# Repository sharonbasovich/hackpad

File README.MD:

# Sharon's Hackpad
This is a macropad that I made for HackClub's Highway program.

## Features
- 16 Switches (4x4 Matrix)
- 16 Neopixels
- An OLED Screen

## Hackpad

## Schematic

## PCB

## Case

## BOM
- 16x Cherry MX Switches
- 16x DSA Keycaps
- 16x 1N4148 Diodes
- 1x 0.91" 128x32 OLED Display
- 1x XIAO RP2040
- 1x Case Bottom Piece
- 1x Case Top Piece
- 4x M3x16mm Screws
- 4x M3x5mx4mm Heatset Inserts

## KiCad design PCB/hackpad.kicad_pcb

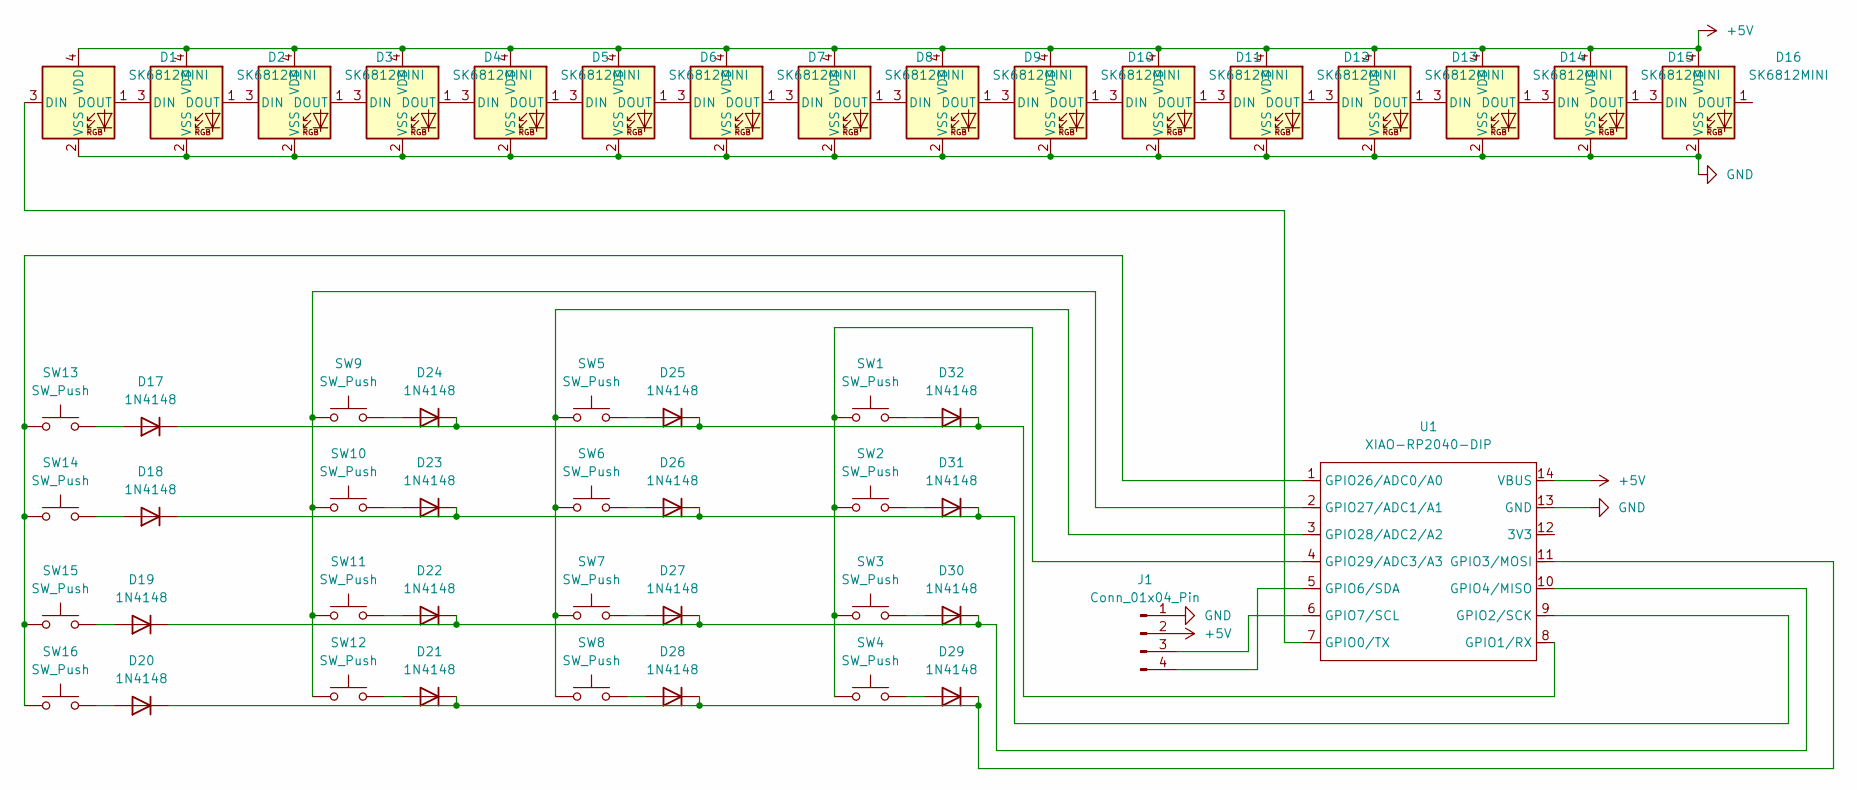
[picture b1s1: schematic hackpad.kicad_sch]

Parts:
D1, D2, D3, D4, D5, D6, D7, D8, D9, D10, D11, D12, D13, D14, D15, D16: SK6812MINI; LED_SK6812MINI_PLCC4_3.5x3.5mm_P1.75mm
D17, D18, D19, D20, D21, D22, D23, D24, D25, D26, D27, D28, D29, D30, D31, D32: 1N4148; D_DO-35_SOD27_P7.62mm_Horizontal
J1: Conn_01x04_Pin; SSD1306-0.91-OLED-4pin-128x32
SW1, SW2, SW3, SW4, SW5, SW6, SW7, SW8, SW9, SW10, SW11, SW12, SW13, SW14, SW15, SW16: SW_Push; SW_Cherry_MX_1.00u_PCB
U1: XIAO-RP2040-DIP

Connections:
+5V: D1.4 (VDD), D2.4 (VDD), D3.4 (VDD), D4.4 (VDD), D5.4 (VDD), D6.4 (VDD), D7.4 (VDD), D8.4 (VDD), D9.4 (VDD), D10.4 (VDD), D11.4 (VDD), D12.4 (VDD), D13.4 (VDD), D14.4 (VDD), D15.4 (VDD), D16.4 (VDD), J1.2, U1.14 (VBUS)
GND: D1.2 (VSS), D2.2 (VSS), D3.2 (VSS), D4.2 (VSS), D5.2 (VSS), D6.2 (VSS), D7.2 (VSS), D8.2 (VSS), D9.2 (VSS), D10.2 (VSS), D11.2 (VSS), D12.2 (VSS), D13.2 (VSS), D14.2 (VSS), D15.2 (VSS), D16.2 (VSS), J1.1, U1.13 (GND)
unnamed: D1.3 (DIN), U1.7 (GPIO0/TX)
unnamed: D1.1 (DOUT), D2.3 (DIN)
unnamed: D2.1 (DOUT), D3.3 (DIN)
unnamed: D3.1 (DOUT), D4.3 (DIN)
unnamed: D4.1 (DOUT), D5.3 (DIN)
unnamed: D5.1 (DOUT), D6.3 (DIN)
unnamed: D6.1 (DOUT), D7.3 (DIN)
unnamed: D7.1 (DOUT), D8.3 (DIN)
unnamed: D8.1 (DOUT), D9.3 (DIN)
unnamed: D9.1 (DOUT), D10.3 (DIN)
unnamed: D10.1 (DOUT), D11.3 (DIN)
unnamed: D11.1 (DOUT), D12.3 (DIN)
unnamed: D12.1 (DOUT), D13.3 (DIN)
unnamed: D13.1 (DOUT), D14.3 (DIN)
unnamed: D14.1 (DOUT), D15.3 (DIN)
unnamed: D15.1 (DOUT), D16.3 (DIN)
unnamed: D17.2 (A), SW13.2
unnamed: D17.1 (K), D24.1 (K), D25.1 (K), D32.1 (K), U1.8 (GPIO1/RX)
unnamed: D18.2 (A), SW14.2
unnamed: D18.1 (K), D23.1 (K), D26.1 (K), D31.1 (K), U1.9 (GPIO2/SCK)
unnamed: D19.2 (A), SW15.2
unnamed: D19.1 (K), D22.1 (K), D27.1 (K), D30.1 (K), U1.10 (GPIO4/MISO)
unnamed: D20.2 (A), SW16.2
unnamed: D20.1 (K), D21.1 (K), D28.1 (K), D29.1 (K), U1.11 (GPIO3/MOSI)
unnamed: D21.2 (A), SW12.2
unnamed: D22.2 (A), SW11.2
unnamed: D23.2 (A), SW10.2
unnamed: D24.2 (A), SW9.2
unnamed: D25.2 (A), SW5.2
unnamed: D26.2 (A), SW6.2
unnamed: D27.2 (A), SW7.2
unnamed: D28.2 (A), SW8.2
unnamed: D29.2 (A), SW4.2
unnamed: D30.2 (A), SW3.2
unnamed: D31.2 (A), SW2.2
unnamed: D32.2 (A), SW1.2
unnamed: J1.3, U1.6 (GPIO7/SCL)
unnamed: J1.4, U1.5 (GPIO6/SDA)
unnamed: SW13.1, SW14.1, SW15.1, SW16.1, U1.1 (GPIO26/ADC0/A0)
unnamed: SW9.1, SW10.1, SW11.1, SW12.1, U1.2 (GPIO27/ADC1/A1)
unnamed: SW5.1, SW6.1, SW7.1, SW8.1, U1.3 (GPIO28/ADC2/A2)
unnamed: SW1.1, SW2.1, SW3.1, SW4.1, U1.4 (GPIO29/ADC3/A3)

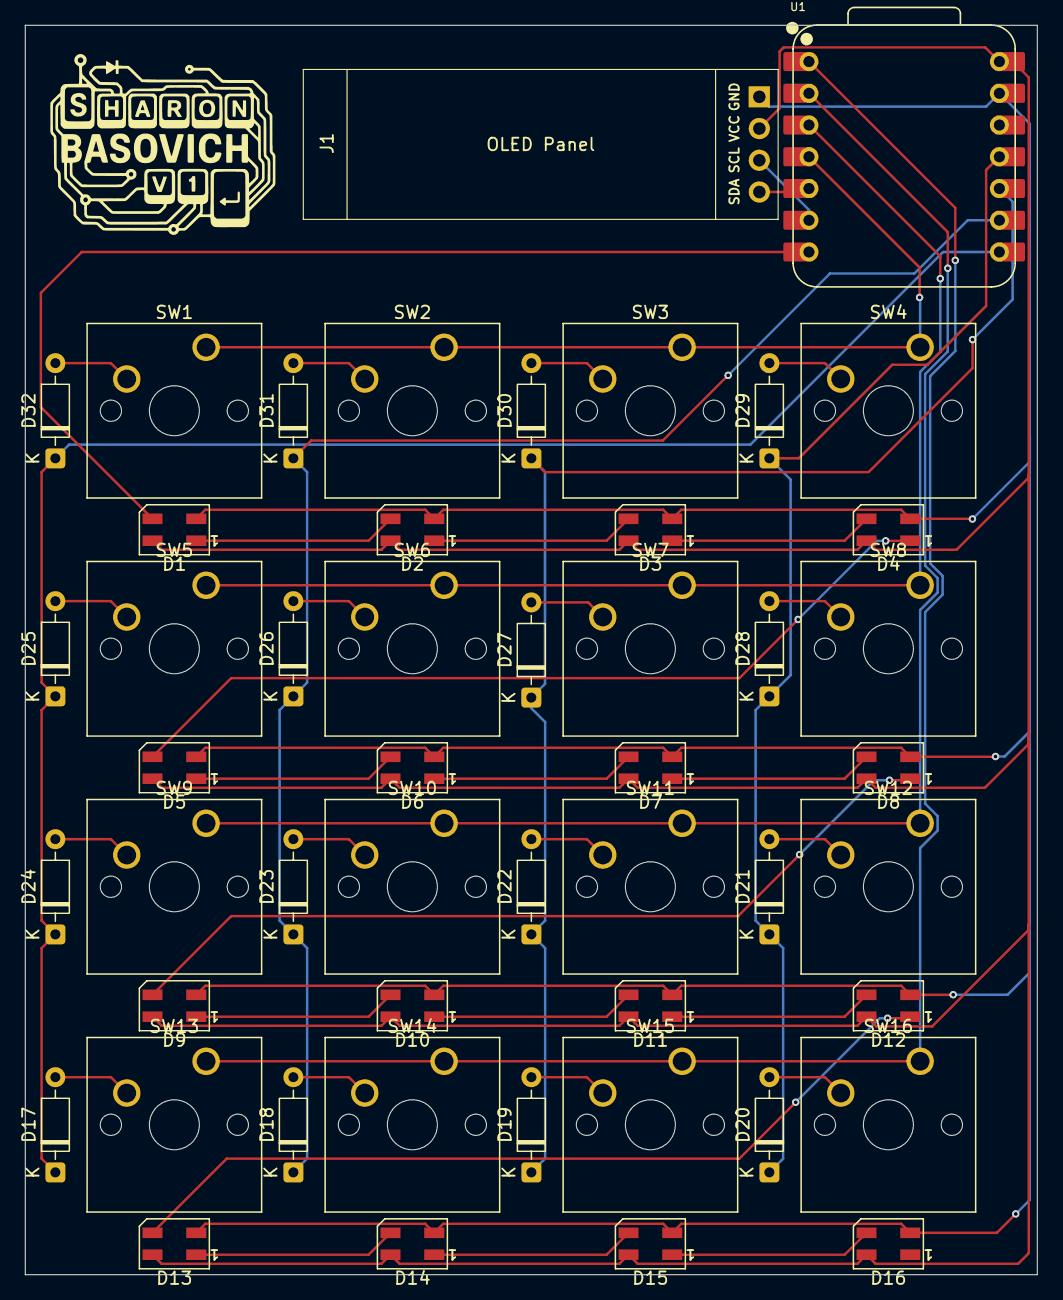
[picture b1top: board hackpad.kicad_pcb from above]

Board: 2 copper layers, 81.0 x 100.0 mm, 50 parts (0 on the bottom side), 44 nets.

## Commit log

2025-07-02 submission
